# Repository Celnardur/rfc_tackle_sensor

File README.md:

# Collegiate Robotic Football Tackle Sensor Hardware

## Cloning the Repo

Open a git bash terminal in the directory of your choosing and call the following command:

`git clone https://github.com/Celnardur/rfc_tackle_sensor.git`

## Developing

This project was created using KiCad v6.  This must be installed prior to editing the project.

## Additional Links

- The firmware for the sensor can be found here: https://github.com/ehunck/rfc_tackle_sensor_firmware
- An example web-serial configuration utility can be found here: https://github.com/ehunck/tackle-sensor-utility

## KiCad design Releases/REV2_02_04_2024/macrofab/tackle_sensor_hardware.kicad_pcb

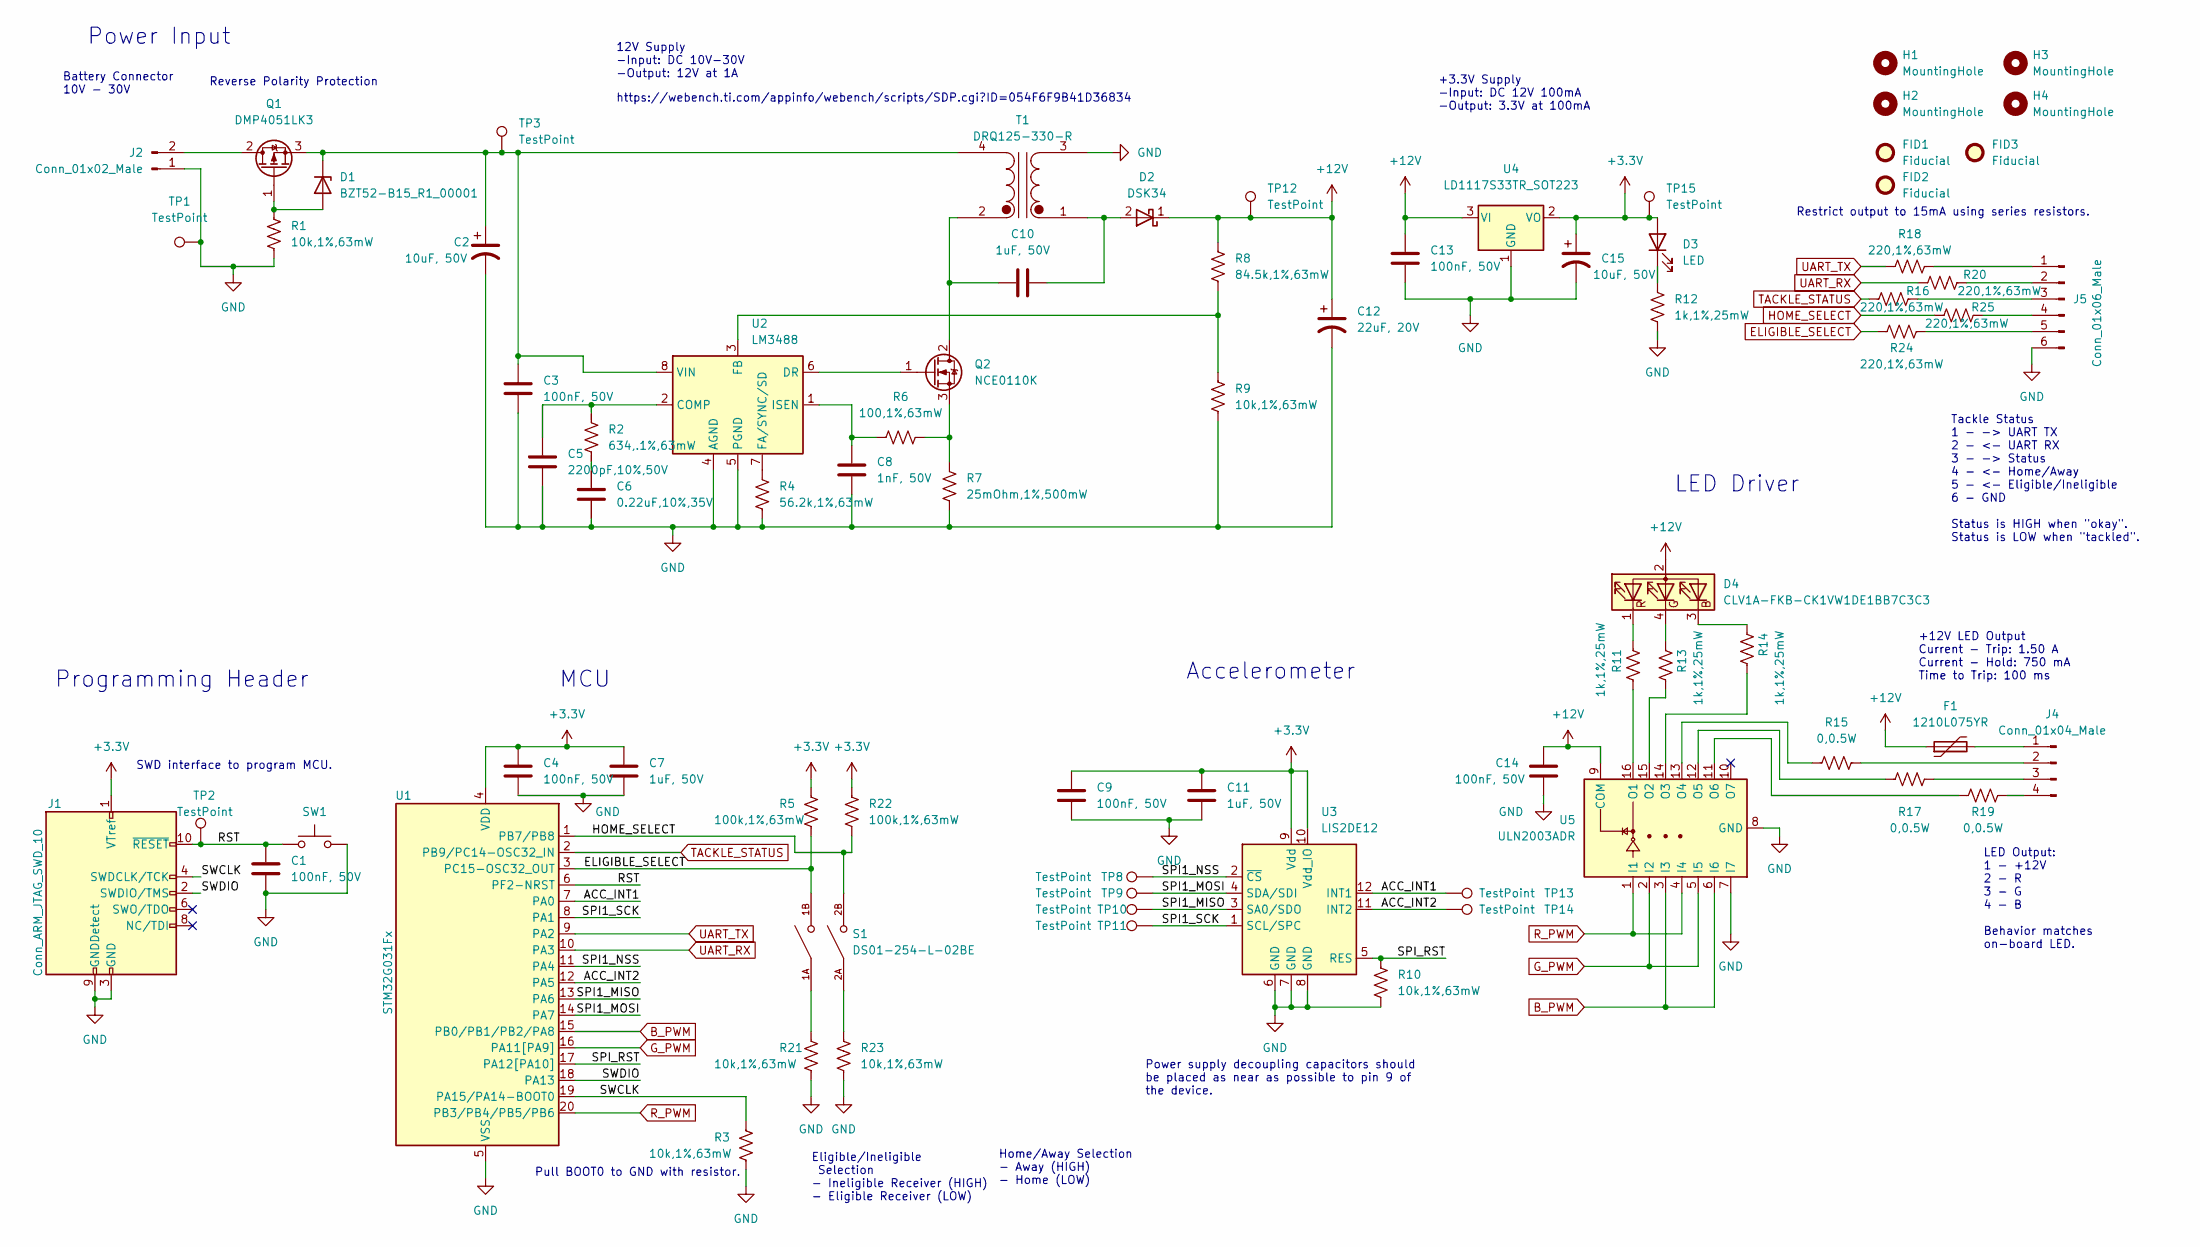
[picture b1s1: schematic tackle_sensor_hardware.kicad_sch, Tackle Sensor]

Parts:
C1, C3, C4, C9, C13, C14: 100nF, 50V; C_0805_2012Metric; MPN CC0805KRX7R9BB104; JLCPN C49678
C2, C15: 10uF, 50V; CP_Elec_6.3x5.8; MPN UUD1H100MCL1GS; JLCPN C308830
C5: 2200pF,10%,50V; C_0402_1005Metric; MPN 0402B222K500CT; JLCPN C338130
C6: 0.22uF,10%,35V; C_0402_1005Metric; MPN CGA2B1X7R1V224KT000F; JLCPN C694490
C7, C10, C11: 1uF, 50V; C_0603_1608Metric; MPN 0603B105K500NT; JLCPN C90540
C8: 1nF, 50V; C_0402_1005Metric; MPN 0402B102K500NT; JLCPN C1523
C12: 22uF, 20V; CP_Elec_6.3x5.9; MPN 20SVP22M; JLCPN C215761
D1: BZT52-B15_R1_00001; D_SOD-123; MPN BZT52-B15_R1_00001; JLCPN C188533
D2: DSK34; D_SOD-123F; MPN DSK34; JLCPN C41029
D3: LED; LED_0603_1608Metric; MPN 19-213/Y2C-CQ2R2L/3T(CY); JLCPN C72038
D4: CLV1A-FKB-CK1VW1DE1BB7C3C3; LED_Cree-PLCC4_3.2x2.8mm_CCW
F1: 1210L075YR; R_1210_3225Metric; MPN 1210L075YR; JLCPN C207046
FID1, FID2, FID3: Fiducial; Fiducial_0.5mm_Mask1.5mm
H1, H2, H3, H4: MountingHole; MountingHole_3.2mm_M3
J1: Conn_ARM_JTAG_SWD_10; 20021121-00010C4LF; MPN 20021121-00010C4LF; JLCPN C150517
J2: Conn_01x02_Male; JST_XH_B2B-XH-A_1x02_P2.50mm_Vertical; MPN B2B-XH-A(LF)(SN); JLCPN C158012
J4: Conn_01x04_Male; JST_XH_B4B-XH-A_1x04_P2.50mm_Vertical; MPN B4B-XH-A(LF)(SN); JLCPN C144395
J5: Conn_01x06_Male; JST_XH_B6B-XH-A_1x06_P2.50mm_Vertical
Q1: DMP4051LK3; TO-252-2; MPN DMP4051LK3-13; JLCPN C397952
Q2: NCE0110K; TO-252-2; MPN NCE0110K; JLCPN C95272
R1, R3, R9, R10, R21, R23: 10k,1%,63mW; R_0402_1005Metric; MPN 0402WGF1002TCE; JLCPN C25744
R2: 634,.1%,63mW; R_0402_1005Metric; MPN FRC0402F6340TS; JLCPN C2998183
R4: 56.2k,1%,63mW; R_0402_1005Metric; MPN 0402WGF5622TCE; JLCPN C54968
R5, R22: 100k,1%,63mW; R_0402_1005Metric
R6: 100,1%,63mW; R_0402_1005Metric; MPN 0402WGF1000TCE; JLCPN C25076
R7: 25mOhm,1%,500mW; R_1206_3216Metric; MPN RL12FTNR200; JLCPN C160920
R8: 84.5k,1%,63mW; R_0402_1005Metric; MPN CR0402FF8452G; JLCPN C100545
R11, R12, R13, R14: 1k,1%,25mW; R_0603_1608Metric; MPN 0603WAF1001T5E; JLCPN C21190
R15, R17, R19: 0,0.5W; R_1210_3225Metric; MPN 1210W2F1000T5E; JLCPN C620661
R16, R18, R20, R24, R25: 220,1%,63mW; R_0402_1005Metric; MPN 0402WGF2200TCE; JLCPN C25091
S1: DS01-254-L-02BE; SW_DS01-254-L-02BE; PARTREV 1.0
SW1: PTS645SL43SMTR92 LFS; SW_SPST_PTS645; MPN PTS645SL43SMTR92LFS; JLCPN C221875
T1: DRQ125-330-R; DRQ125-150-R; MPN DRQ125-330-R
TP1, TP3, TP12, TP15: TestPoint; TestPoint_Pad_D1.0mm
TP2, TP8, TP9, TP10, TP11, TP13, TP14: TestPoint; test_point
U1: STM32G031Fx; TSSOP-20_4.4x6.5mm_P0.65mm; MPN STM32G031F8P6; JLCPN C529334
U2: LM3488; VSSOP-8_3.0x3.0mm_P0.65mm; MPN LM3488MM/NOPB; JLCPN C80773
U3: LIS2DE12; LGA-12_2x2mm_P0.5mm; MPN LIS2DE12TR; JLCPN C155639
U4: LD1117S33TR_SOT223; SOT-223-3_TabPin2; MPN LD1117S33TR; JLCPN C86781
U5: ULN2003ADR; SOIC-16_3.9x9.9mm_P1.27mm; MPN ULN2003ADR; JLCPN C7512

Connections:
+3V3: C4.1, C7.1, C9.1, C11.1, C15.1, D3.2 (A), J1.1 (VTref), R5.1, R22.1, TP15.1, U1.4 (VDD), U3.9 (Vdd), U3.10 (Vdd_IO), U4.2 (VO)
+12V: C12.1, C13.1, C14.1, D2.1 (K), D4.2 (RK), F1.1, R8.1, TP12.1, U4.3 (VI), U5.9 (COM)
/ACC_INT1: TP13.1, U1.7 (PA0), U3.12 (INT1)
/ACC_INT2: TP14.1, U1.12 (PA5), U3.11 (INT2)
/RST: C1.1, J1.10 (~RESET), SW1.1, TP2.1, U1.6 (PF2-NRST)
/SPI1_MISO: TP10.1, U1.13 (PA6), U3.3 (SA0/SDO)
/SPI1_MOSI: TP9.1, U1.14 (PA7), U3.4 (SDA/SDI)
/SPI1_NSS: TP8.1, U1.11 (PA4), U3.2 (~CS)
/SPI1_SCK: TP11.1, U1.8 (PA1), U3.1 (SCL/SPC)
/SPI_RST: R10.1, U1.17 (PA12[PA10]), U3.5 (RES)
/SWCLK: J1.4 (SWDCLK/TCK), R3.2, U1.19 (PA15/PA14-BOOT0)
/SWDIO: J1.2 (SWDIO/TMS), U1.18 (PA13)
B_PWM: U1.15 (PB0/PB1/PB2/PA8), U5.3 (I3), U5.6 (I6)
ELIGIBLE_SELECT: R5.2, R24.1, S1.1B, U1.3 (PC15-OSC32_OUT)
GND: C1.2, C2.2, C3.2, C4.2, C5.2, C6.2, C7.2, C8.2, C9.2, C11.2, C12.2, C13.2, C14.2, C15.2, J1.3 (GND), J1.5 (GND), J1.9 (GNDDetect), J2.1, J5.6, R1.2, R3.1, R4.2, R7.2, R9.2, R10.2, R12.2, R21.2, R23.2, SW1.2, T1.3 (SA), TP1.1, U1.5 (VSS), U2.4 (AGND), U2.5 (PGND), U3.6 (GND), U3.7 (GND), U3.8 (GND), U4.1 (GND), U5.7 (I7), U5.8 (GND)
G_PWM: U1.16 (PA11[PA9]), U5.2 (I2), U5.5 (I5)
HOME_SELECT: R22.2, R25.1, S1.2B, U1.1 (PB7/PB8)
unnamed: C2.1, C3.1, D1.1 (K), Q1.3 (S), T1.4 (SB), TP3.1, U2.8 (VIN)
unnamed: C5.1, R2.1, U2.2 (COMP)
unnamed: C6.1, R2.2
unnamed: C8.1, R6.1, U2.1 (ISEN)
unnamed: C10.1, D2.2 (A), T1.1 (AA)
unnamed: D1.2 (A), Q1.1 (G), R1.1
unnamed: D3.1 (K), R12.1
unnamed: D4.1 (A), R11.1
unnamed: D4.3 (GK), R14.1
unnamed: D4.4 (BK), R13.1
unnamed: F1.2, J4.1
unnamed: J2.2, Q1.2 (D)
unnamed: J4.2, R15.1
unnamed: J4.3, R17.1
unnamed: J4.4, R19.1
unnamed: J5.1, R18.2
unnamed: J5.2, R20.2
unnamed: J5.3, R16.2
unnamed: J5.4, R25.2
unnamed: J5.5, R24.2
unnamed: Q2.1 (G), U2.6 (DR)
unnamed: R4.1, U2.7 (FA/SYNC/SD)
unnamed: R8.2, R9.1, U2.3 (FB)
unnamed: R11.2, U5.16 (O1)
unnamed: R13.2, U5.15 (O2)
unnamed: R14.2, U5.14 (O3)
unnamed: R15.2, U5.13 (O4)
unnamed: R17.2, U5.12 (O5)
unnamed: R19.2, U5.11 (O6)
unnamed: R21.1, S1.1A
unnamed: R23.1, S1.2A
R_PWM: U1.20 (PB3/PB4/PB5/PB6), U5.1 (I1), U5.4 (I4)
TACKLE_STATUS: R16.1, U1.2 (PB9/PC14-OSC32_IN)
UART_RX: R20.1, U1.10 (PA3)
UART_TX: R18.1, U1.9 (PA2)

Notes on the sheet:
Programming Header
Eligible/Ineligible Selection - Ineligible Receiver (HIGH) - Eligible Receiver (LOW)
LED Driver
12V Supply -Input: DC 10V-30V -Output: 12V at 1A
Home/Away Selection - Away (HIGH) - Home (LOW)
+12V LED Output Current - Trip: 1.50 A Current - Hold: 750 mA Time to Trip: 100 ms
+3.3V Supply -Input: DC 12V 100mA -Output: 3.3V at 100mA
Power Input
Tackle Status 1 - -> UART TX 2 - <- UART RX 3 - -> Status 4 - <- Home/Away 5 - <- Eligible/Ineligible 6 - GND Status is HIGH when "okay". Status is LOW when "tackled".
LED Output: 1 - +12V 2 - R 3 - G 4 - B Behavior matches on-board LED.
Pull BOOT0 to GND with resistor.
Battery Connector 10V - 30V
SWD interface to program MCU.
Restrict output to 15mA using series resistors.
MCU
Reverse Polarity Protection
Accelerometer
https://webench.ti.com/appinfo/webench/scripts/SDP.cgi?ID=054F6F9B41D36834
Power supply decoupling capacitors should be placed as near as possible to pin 9 of the device.

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
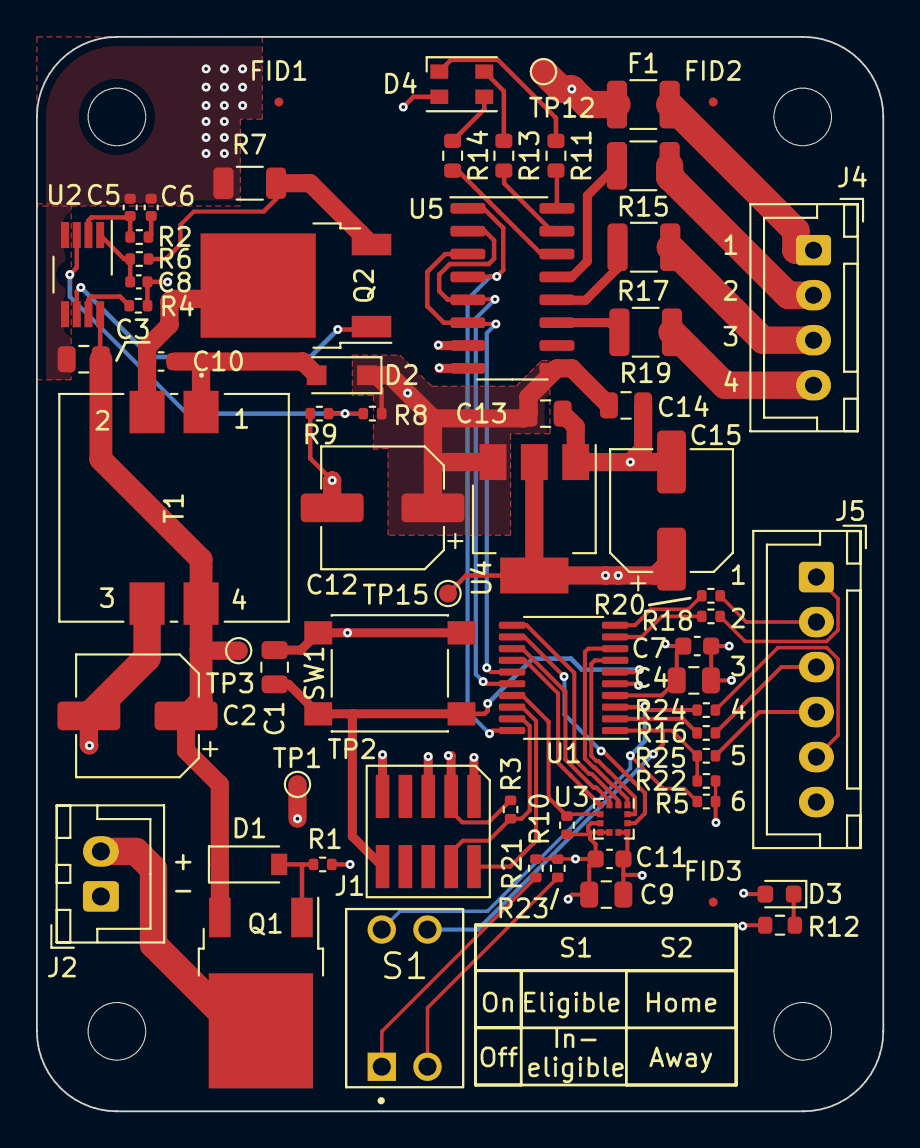
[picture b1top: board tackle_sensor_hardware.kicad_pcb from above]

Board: 4 copper layers, 47.0 x 59.7 mm, 77 parts (0 on the bottom side), 54 nets.

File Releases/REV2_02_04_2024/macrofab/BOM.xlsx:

Designator | Value | Footprint | Populate | MPN | Manufacturer | MPN | Manufacturer
C1 | 100nF, 50V | C_0805_2012Metric | 1 | CC0805KRX7R9BB104 | Yageo
C10 | 1uF, 50V | C_0603_1608Metric | 1 | CL10A105KB8NNNC | Samsung
C11 | 1uF, 50V | C_0603_1608Metric | 1 | CL10A105KB8NNNC | Samsung
C12 | 22uF, 20V | CP_Elec_6.3x5.9 | 1 | 20SVP22M | Panasonic
C13 | 100nF, 50V | C_0805_2012Metric | 1 | CC0805KRX7R9BB104 | Yageo
C14 | 100nF, 50V | C_0805_2012Metric | 1 | CC0805KRX7R9BB104 | Yageo
C15 | 10uF, 50V | CP_Elec_6.3x5.8 | 1 | UUD1H100MCL1GS | Nichicon
C2 | 10uF, 50V | CP_Elec_6.3x5.8 | 1 | UUD1H100MCL1GS | Nichicon
C3 | 100nF, 50V | C_0805_2012Metric | 1 | CC0805KRX7R9BB104 | Yageo
C4 | 100nF, 50V | C_0805_2012Metric | 1 | CC0805KRX7R9BB104 | Yageo
C5 | 2200pF,10%,50V | C_0402_1005Metric | 1 | 0402B222K500CT | Walsin Technologies
C6 | 0.22uF,10%,35V | C_0402_1005Metric | 1 | CGA2B1X7R1V224KT000F | TDK | CGA2B1X7R1V224K050BE | TDK
C7 | 1uF, 50V | C_0603_1608Metric | 1 | CL10A105KB8NNNC | Samsung
C8 | 1nF, 50V | C_0402_1005Metric | 1 | 0402B102K500NT | Knowles Acoustics | C1005X7R1H102K050BA | TDK
C9 | 100nF, 50V | C_0805_2012Metric | 1 | CC0805KRX7R9BB104 | Yageo
D1 | BZT52-B15_R1_00001 | D_SOD-123 | 1 | BZT52-B15_R1_00001 | Panjit
D2 | DSK34 | D_SOD-123F | 1 | SBA340AL_R1_00001 | Panjit
D3 | LED | LED_0603_1608Metric | 1 | B1911UY--20D000114U1930 | Harvatek
D4 | CLV1A-FKB-CK1VW1DE1BB7C3C3 | LED_Cree-PLCC4_3.2x2.8mm_CCW | 1 | CLV1A-FKB-CK1VW1DE1BB7C3C3 | Wolfspeed
F1 | 1210L075YR | R_1210_3225Metric | 1 | 1210L075YR | Littelfuse
FID1 | Fiducial | Fiducial_0.5mm_Mask1.5mm | 0
FID2 | Fiducial | Fiducial_0.5mm_Mask1.5mm | 0
FID3 | Fiducial | Fiducial_0.5mm_Mask1.5mm | 0
H1 | MountingHole | MountingHole_3.2mm_M3 | 0
H2 | MountingHole | MountingHole_3.2mm_M3 | 0
H3 | MountingHole | MountingHole_3.2mm_M3 | 0
H4 | MountingHole | MountingHole_3.2mm_M3 | 0
J1 | Conn_ARM_JTAG_SWD_10 | 20021121-00010C4LF | 1 | 20021121-00010C4LF | Amphenol Communications Solutions
J2 | Conn_01x02_Male | JST_XH_B2B-XH-A_1x02_P2.50mm_Vertical | 1 | B2B-XH-A | JST
J4 | Conn_01x04_Male | JST_XH_B4B-XH-A_1x04_P2.50mm_Vertical | 1 | B4B-XH-A | JST
J5 | Conn_01x06_Male | JST_XH_B6B-XH-A_1x06_P2.50mm_Vertical | 1 | B6B-XH-A | JST
Q1 | DMP4051LK3 | TO-252-2 | 1 | DMP4051LK3-13 | Diodes Inc.
Q2 | NCE0110K | TO-252-2 | 1 | NCE0110K | Wuxi | RFD3055LESM9A | onsemi
R1 | 10k,1%,63mW | R_0402_1005Metric | 1 | 0402WGF1002TCE | Royal Ohm | RC0402FR-0710KP | Yageo
R10 | 10k,1%,63mW | R_0402_1005Metric | 1 | 0402WGF1002TCE | Royal Ohm | RC0402FR-0710KP | Yageo
R11 | 1k,1%,25mW | R_0603_1608Metric | 1 | 0603WAF1001T5E | Royal Ohm | RNCP0603FTD1K00 | Stackpole Electronics
R12 | 1k,1%,25mW | R_0603_1608Metric | 1 | 0603WAF1001T5E | Royal Ohm | RNCP0603FTD1K00 | Stackpole Electronics
R13 | 1k,1%,25mW | R_0603_1608Metric | 1 | 0603WAF1001T5E | Royal Ohm | RNCP0603FTD1K00 | Stackpole Electronics
R14 | 1k,1%,25mW | R_0603_1608Metric | 1 | 0603WAF1001T5E | Royal Ohm | RNCP0603FTD1K00 | Stackpole Electronics
R15 | 0,0.5W | R_1210_3225Metric | 1 | 1210W2F1000T5E | Uniroyal | RMCF1210ZT0R00 | Stackpole Electronics
R16 | 220,1%,63mW | R_0402_1005Metric | 1 | 0402WGF2200TCE | Royal Ohm | RC0402FR-07220RL | Yageo
R17 | 0,0.5W | R_1210_3225Metric | 1 | 1210W2F1000T5E | Uniroyal | RMCF1210ZT0R00 | Stackpole Electronics
R18 | 220,1%,63mW | R_0402_1005Metric | 1 | 0402WGF2200TCE | Royal Ohm | RC0402FR-07220RL | Yageo
R19 | 0,0.5W | R_1210_3225Metric | 1 | 1210W2F1000T5E | Uniroyal | RMCF1210ZT0R00 | Stackpole Electronics
R2 | 634,.1%,63mW | R_0402_1005Metric | 1 | RC0402FR-07634RL | Yageo
R20 | 220,1%,63mW | R_0402_1005Metric | 1 | 0402WGF2200TCE | Royal Ohm | RC0402FR-07220RL | Yageo
R21 | 10k,1%,63mW | R_0402_1005Metric | 1 | 0402WGF1002TCE | Royal Ohm | RC0402FR-0710KP | Yageo
R22 | 100k,1%,63mW | R_0402_1005Metric | 1 | RT0402BRE07100KL | Yageo
R23 | 10k,1%,63mW | R_0402_1005Metric | 1 | 0402WGF1002TCE | Royal Ohm | RC0402FR-0710KP | Yageo
R24 | 220,1%,63mW | R_0402_1005Metric | 1 | 0402WGF2200TCE | Royal Ohm | RC0402FR-07220RL | Yageo
R25 | 220,1%,63mW | R_0402_1005Metric | 1 | 0402WGF2200TCE | Royal Ohm | RC0402FR-07220RL | Yageo
R3 | 10k,1%,63mW | R_0402_1005Metric | 1 | 0402WGF1002TCE | Royal Ohm | RC0402FR-0710KP | Yageo
R4 | 56.2k,1%,63mW | R_0402_1005Metric | 1 | RC0402FR-0756K2L | Yageo
R5 | 100k,1%,63mW | R_0402_1005Metric | 1 | RT0402BRE07100KL | Yageo
R6 | 100,1%,63mW | R_0402_1005Metric | 1 | 0402WGF1000TCE | Royal Ohm | RC0402FR-13100RL | Yageo
R7 | 25mOhm,1%,500mW | R_1206_3216Metric | 1 | CSR1206FK25L0 | Stackpole Electronics
R8 | 84.5k,1%,63mW | R_0402_1005Metric | 1 | RC0402FR-0784K5L | Yageo
R9 | 10k,1%,63mW | R_0402_1005Metric | 1 | 0402WGF1002TCE | Royal Ohm | RC0402FR-0710KP | Yageo
S1 | DS01-254-L-02BE | SW_DS01-254-L-02BE | 1 | DS01-254-L-02BE | CUI Devices
SW1 | PTS645SL43SMTR92 LFS | SW_SPST_PTS645 | 1 | PTS645SL43SMTR92LFS | C&K Components
T1 | DRQ125-330-R | DRQ125-150-R | 1 | DRQ125-330-R | Eaton
TP1 | TestPoint | TestPoint_Pad_D1.0mm | 0
TP10 | TestPoint | test_point | 0
TP11 | TestPoint | test_point | 0
TP12 | TestPoint | TestPoint_Pad_D1.0mm | 0
TP13 | TestPoint | test_point | 0
TP14 | TestPoint | test_point | 0
TP15 | TestPoint | TestPoint_Pad_D1.0mm | 0
TP2 | TestPoint | test_point | 0
TP3 | TestPoint | TestPoint_Pad_D1.0mm | 0
TP8 | TestPoint | test_point | 0
TP9 | TestPoint | test_point | 0
U1 | STM32G031Fx | TSSOP-20_4.4x6.5mm_P0.65mm | 1 | STM32G031F8P6 | STMicroelectronics
U2 | LM3488 | VSSOP-8_3.0x3.0mm_P0.65mm | 1 | LM3488MM/NOPB | Texas Instruments
U3 | LIS2DE12 | LGA-12_2x2mm_P0.5mm | 1 | LIS2DE12TR | STMicroelectronics
U4 | LD1117S33TR_SOT223 | SOT-223-3_TabPin2 | 1 | LD1117S33TR | STMicroelectronics
U5 | ULN2003ADR | SOIC-16_3.9x9.9mm_P1.27mm | 1 | ULN2003ADR | Texas Instruments

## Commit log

2022-04-10 Set up KiCad Project
2022-04-10 added README
2022-04-10 (WIP) added some components and basic schematic pieces.
2022-04-10 (WIP) added prog header to schematic and added some WIP notes.
2022-04-10 added mounting holes
2022-04-10 added on-board LEDs
2022-04-11 updated connectors, added 0 ohm resistors
2022-04-11 added pinout to MCU
2022-04-12 added eFuse, added mosfet, added footprints
2022-04-13 Picked most RC components and footprints
2022-04-13 add graphic
2022-04-15 updated component placement and board size, cleaning up schamtic and part selection.
2022-04-15 routing in progress.
2022-04-15 update reset button, add decoupling caps for MCU.
2022-04-16 added PTC
2022-04-18 route board
2022-04-19 finish route, add release pacakage
2022-04-19 add BOM
2022-08-07 updated some parts with instock components
2022-09-01 Updating schematic and layout for manufacture with LCSC.
2022-10-08 updating the BOM
2022-10-23 rerouted PCB after changes
2022-10-25 adding release v0.1
2023-01-23 - updates for release v0.1
2023-03-04 - add reference PDFs and dimensions to the layout
2023-03-04 - change page size to legal
2023-03-04 - added additional notes to the reference_sheet and the schematic sheet
2023-03-04 - update cable assembly link
2023-08-30 - update PCB and schematic with new switch plus added 3d models
2023-08-31 - finish routing
2023-09-01 - updating layout and releasing
2023-09-26 - release artifacts
2023-09-26 -license and readme
2023-09-26 - readme fix
2024-01-10 - regen. schematic with Logic level updates
2024-02-05 - Change SPI RST to pull down to 10k. Added line from MCU to toggle the ACCEL reset. Added release files REV2

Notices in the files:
parts and their libraries:
Copyright 2021 Accelerated Designs. All rights reserved.
